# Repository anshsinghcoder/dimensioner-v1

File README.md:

# dimensioner v1 
MAAP 1 is a automated DIM system that costs 10 times less compared to the current options . 
it is aluminum blasted but u can completely use fibre 3d printing for this . i have removed the wieging scale from research that most users dont need it. 

Overview:
MAAP-1 Utilizes a custom ESP32-based PCB, 3 LiDAR sensors to  instantly calculate the length ,  height and width of any parcel .
Designed for logistics, warehouses . i have included electronics components make sure u add it in your cad library. sorry though not much room for customisation many pins are used , feel free to play around with the scematics if u wish
- it also features a camera system which snaps images along side the dim . how ever please make sure the camera module u use comes with a sd slot or just add a pin. 

Hardware Architecture
1. Custom PCB (KiCad)
The brains of the operation is a custom PCB designed to be attached anywhere in the frame it has a 2 hole enclosure that is also included .

Microcontroller: ESP32-WROOM
Power: 5V input, regulated to 3.3V via AMS1117 for logic.

2. Mechanical Structure
  - T-slot aluminum extrusion holding the overhead LiDAR .
  - Dual forward-facing structural arms housing inward-facing LiDARs 
  - control box housing the custom PCB, screen, buttons, and thermal printer.

Repository Structure

MAAP-1:
- Firmware             # PLEASE CALIBRATE AS PER NEEDS 
- Hardware            # KiCad PCB design files, Schematics, and Gerbers
- Mechanical           # 3D files for the enclosure and arms PLEASE ADD THE PCB ENCLOSURE AND SCREEN WHERE YOU NEED .
- README.md             # Project documentation

Here is the complete Bill of Materials (BOM) to build your own.
IF U WANT AMOUNTS IN DOLLARS PLEASE REFER TO BOM.CSV 

| Component | Qty | Est. Price | Link / Source |
| --- | --- | --- | --- |
| **ESP32 WROOM-32 Dev Board** | 1 | ₹1850 | [Robu.in](https://robu.in/product/nodemcu-esp-32s-esp-32e-wifi-serial-wifi-bluetooth/?utm_source=gemini) |
| **ESP32-CAM Module** | 1 | ₹2499 | [Robu.in](https://robu.in/product/esp32-cam-wifi-module-bluetooth-with-ov2640-camera-module-2mp/?utm_source=gemini) |
| **VL53L0X ToF LiDAR Sensor** | 3 | ₹4500 *(₹1499 each)* | [Robu.in](https://www.google.com/search?q=https://robu.in/product/vl53l0x-time-of-flight-tof-laser-ranging-sensor-v2/&utm_source=gemini) |
| **1.3" I2C OLED Display (White)** | 1 | ₹299 | [Robu.in](https://robu.in/product/1-3-inch-i2c-oled-display-module-4-pin-white/?utm_source=gemini) |
| **Mechanical Switch / Arcade Button** | 1 | ₹150 | Local Electronics Market |
| **5V 3A Power Adapter** | 1 | ₹250 | Local Electronics Market |
| **LED Strip / Ring Light (6000K)** | 1 | ₹150 | Local Electronics Market |
| **Aluminum 2020 V-Slot Extrusions** | 2m | ₹1000 | Local Hardware Supplier |
| **Clear Polycarbonate/Acrylic Sheets** | 1 | ₹900 | Local Laser-Cutting Shop |
| **Custom PCB (Matte Black + ENIG)** | 5 | ₹1850 | [JLCPCB](https://jlcpcb.com?utm_source=gemini) |
| **Hardware Kit (T-Nuts, M4 Bolts, Brackets)** | 1 | ₹350 | Local Hardware Supplier |

* **Total Estimated Build Cost:** **~₹23,500 (approx. $235 USD)**

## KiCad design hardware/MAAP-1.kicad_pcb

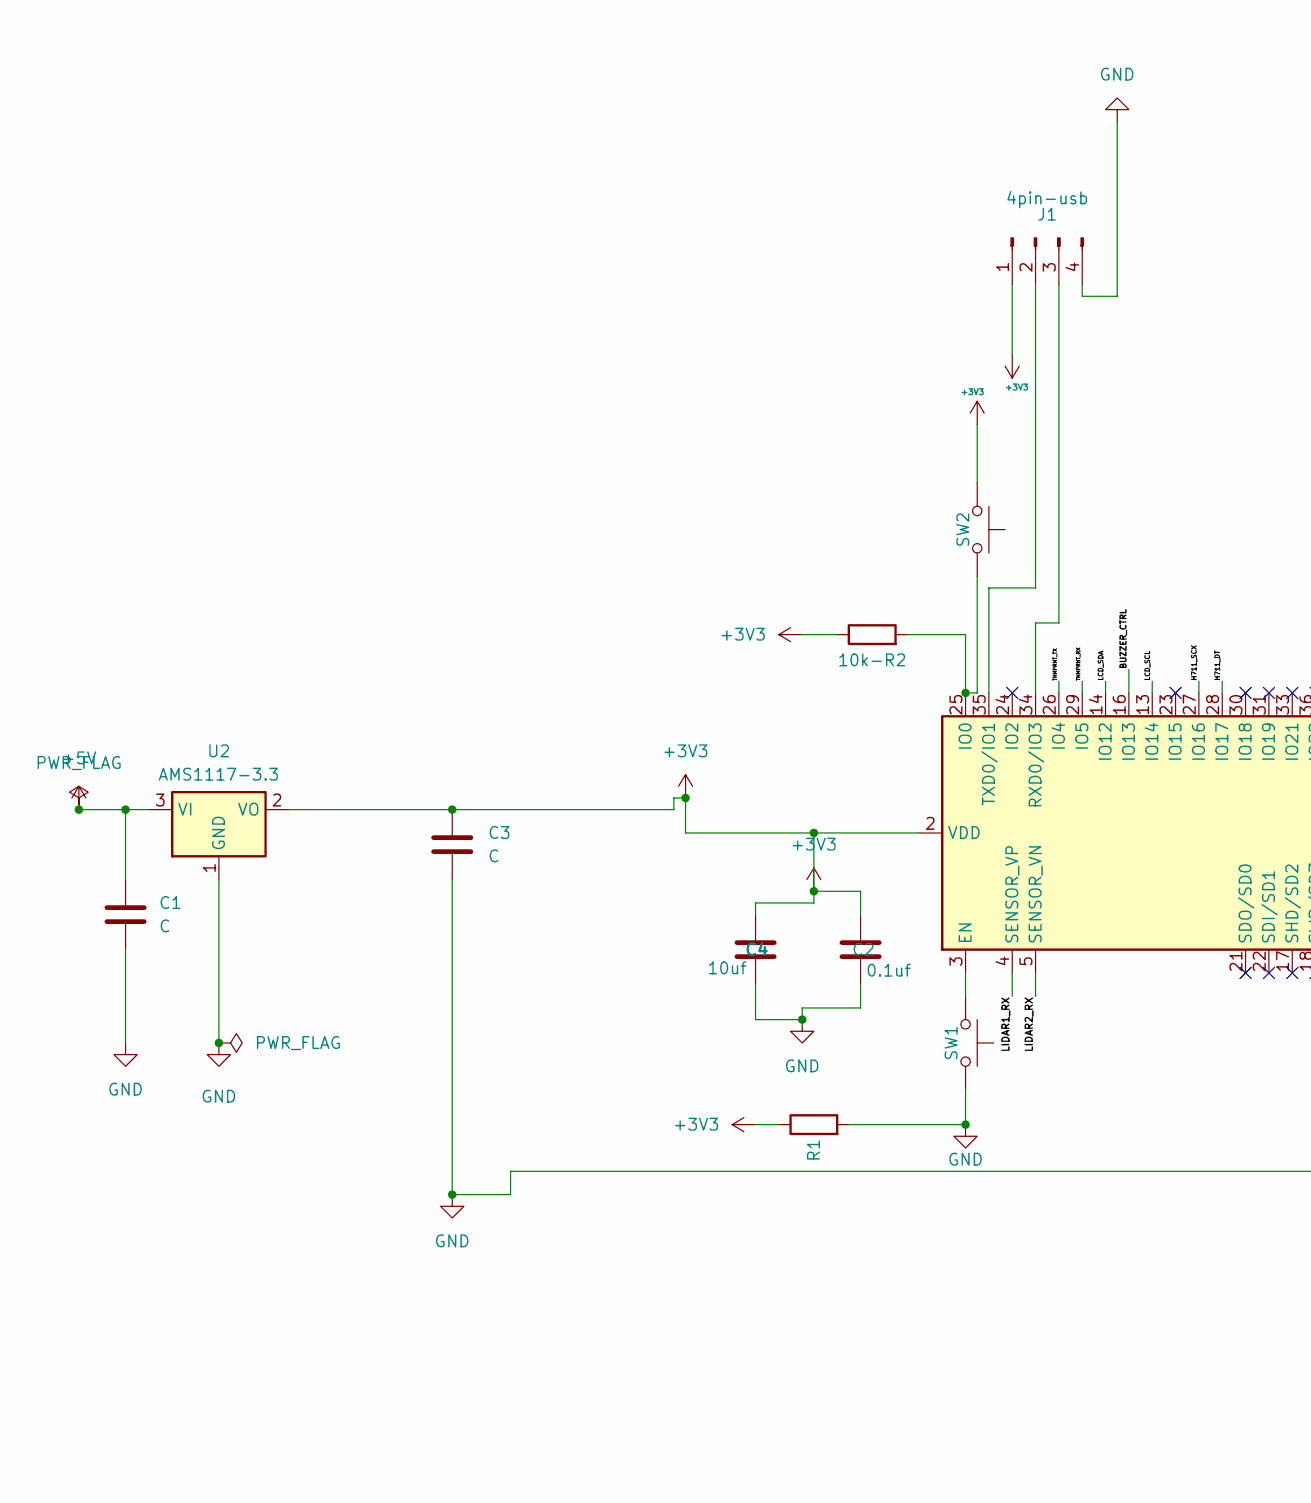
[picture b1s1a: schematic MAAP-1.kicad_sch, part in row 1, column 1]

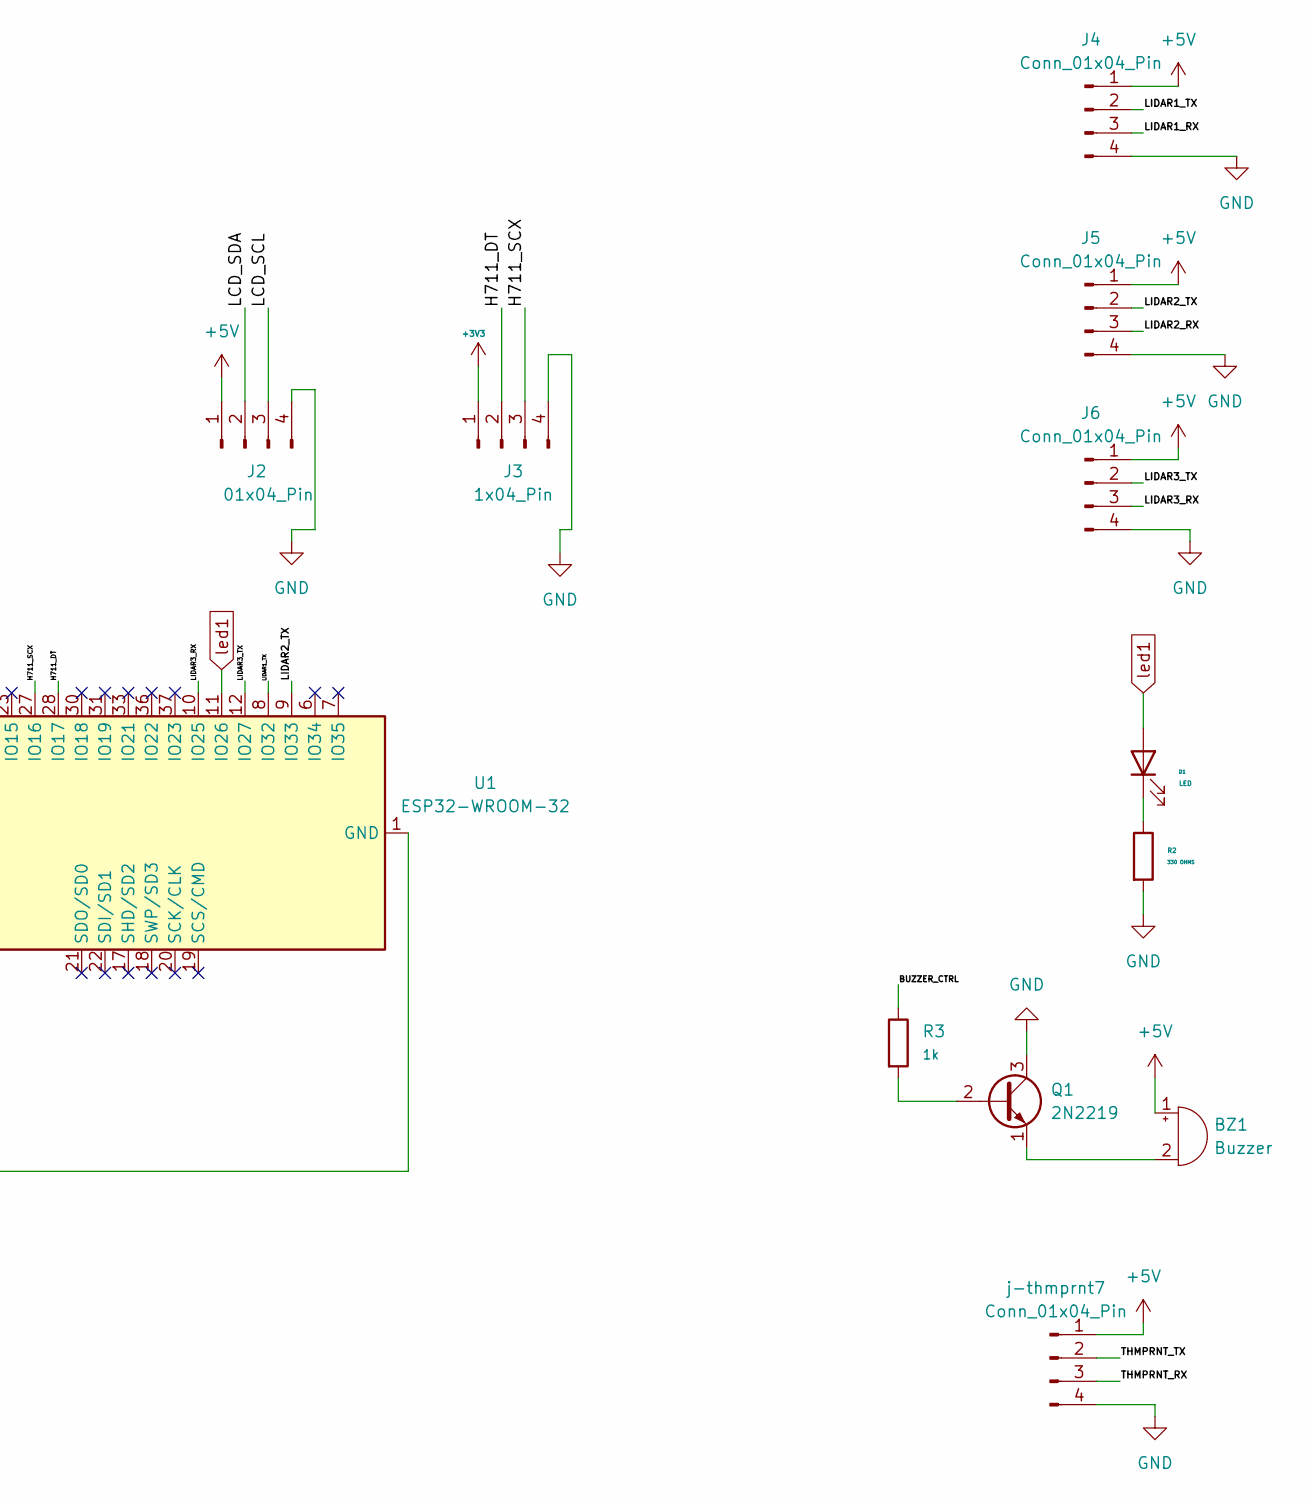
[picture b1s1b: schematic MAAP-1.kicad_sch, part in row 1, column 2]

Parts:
10k-R2: 10k; R_Axial_DIN0207_L6.3mm_D2.5mm_P10.16mm_Horizontal
BZ1: Buzzer; Buzzer_12x9.5RM7.6
C1, C3: C; C_Disc_D5.0mm_W2.5mm_P5.00mm
C2: 0.1uf; C_Disc_D5.0mm_W2.5mm_P5.00mm
C4: 10uf; C_Disc_D5.0mm_W2.5mm_P5.00mm
D1: LED; LED_D5.0mm
J1: 4pin-usb; PinHeader_1x04_P2.54mm_Vertical
J2: 01x04_Pin; PinHeader_1x04_P2.54mm_Vertical
J3: 1x04_Pin; PinHeader_1x04_P2.54mm_Vertical
J4, J5, J6: Conn_01x04_Pin; PinHeader_1x04_P2.54mm_Vertical
Q1: 2N2219; TO-39-3
R1: 10k-r1; R_Axial_DIN0207_L6.3mm_D2.5mm_P10.16mm_Horizontal
R2: 330 OHMS; R_Axial_DIN0207_L6.3mm_D2.5mm_P10.16mm_Horizontal
R3: 1k; R_Axial_DIN0207_L6.3mm_D2.5mm_P10.16mm_Horizontal
SW1, SW2: SW_Push; SW_PUSH_6mm
U1: ESP32-WROOM-32
U2: AMS1117-3.3; SOT-223-3_TabPin2
j-thmprnt7: Conn_01x04_Pin; PinHeader_1x04_P2.54mm_Vertical

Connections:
+3V3: 10k-R2.1, C2.1, C3.1, C4.1, J1.1, J3.1, R1.1, SW2.1, U1.2 (VDD), U2.2 (VO)
+5V: BZ1.1 (+), C1.1, J2.1, J4.1, J5.1, J6.1, U2.3 (VI), j-thmprnt7.1
/BUZZER_CTRL: R3.1, U1.16 (IO13)
/H711_DT: J3.2, U1.28 (IO17)
/H711_SCX: J3.3, U1.27 (IO16)
/LCD_SCL: J2.3, U1.13 (IO14)
/LCD_SDA: J2.2, U1.14 (IO12)
/LIDAR1_RX: J4.3, U1.4 (SENSOR_VP)
/LIDAR1_TX: J4.2, U1.8 (IO32)
/LIDAR2_RX: J5.3, U1.5 (SENSOR_VN)
/LIDAR2_TX: J5.2, U1.9 (IO33)
/LIDAR3_RX: J6.3, U1.10 (IO25)
/LIDAR3_TX: J6.2, U1.12 (IO27)
/THMPRNT_RX: U1.29 (IO5), j-thmprnt7.3
/THMPRNT_TX: U1.26 (IO4), j-thmprnt7.2
GND: C1.2, C2.2, C3.2, C4.2, J1.4, J2.4, J3.4, J4.4, J5.4, J6.4, Q1.3 (C), R1.2, R2.2, SW1.2, U1.1 (GND), U1.15 (GND), U1.38 (GND), U1.39 (GND), U2.1 (GND), j-thmprnt7.4
unnamed: BZ1.2 (-), Q1.1 (E)
unnamed: D1.1 (K), R2.1
unnamed: J1.2, U1.35 (TXD0/IO1)
unnamed: J1.3, U1.34 (RXD0/IO3)
unnamed: Q1.2 (B), R3.2
unnamed: SW1.1, U1.3 (EN)
unnamed: 10k-R2.2, SW2.2, U1.25 (IO0)
led1: D1.2 (A), U1.11 (IO26)

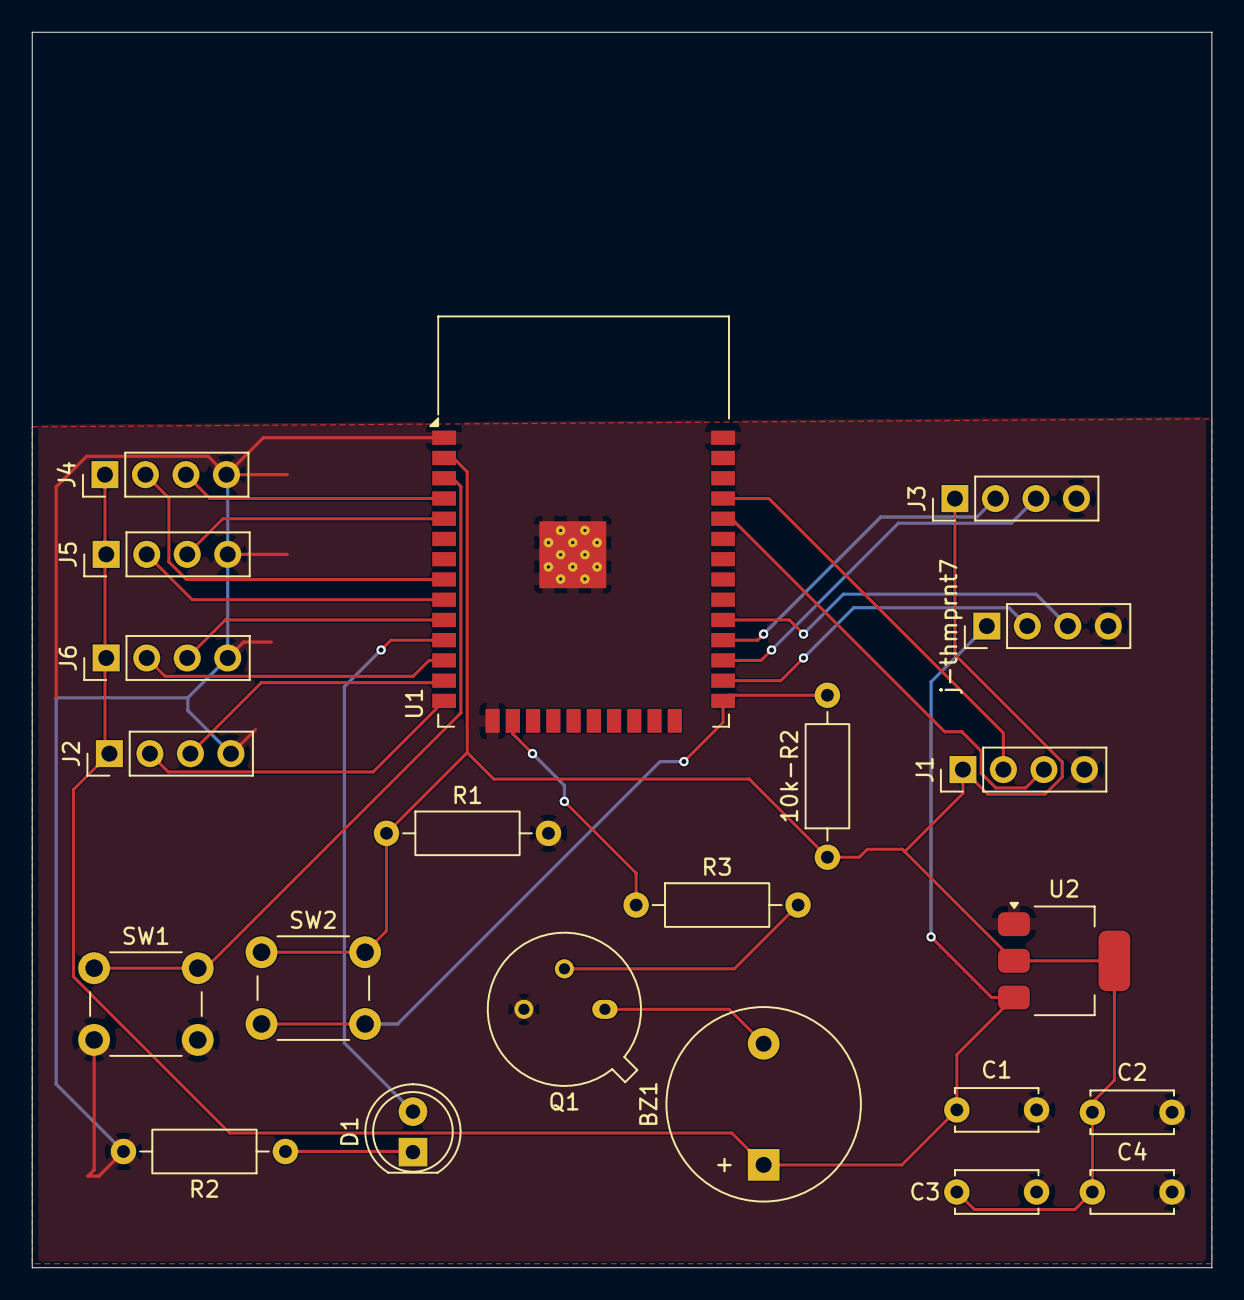
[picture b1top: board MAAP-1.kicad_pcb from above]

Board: 2 copper layers, 74.0 x 77.5 mm, 22 parts (0 on the bottom side), 24 nets.
